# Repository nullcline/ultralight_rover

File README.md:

# ultralight_rover
[design team] CAD files, a PCB, and firmware for an autonomous, and ultra light weight rover

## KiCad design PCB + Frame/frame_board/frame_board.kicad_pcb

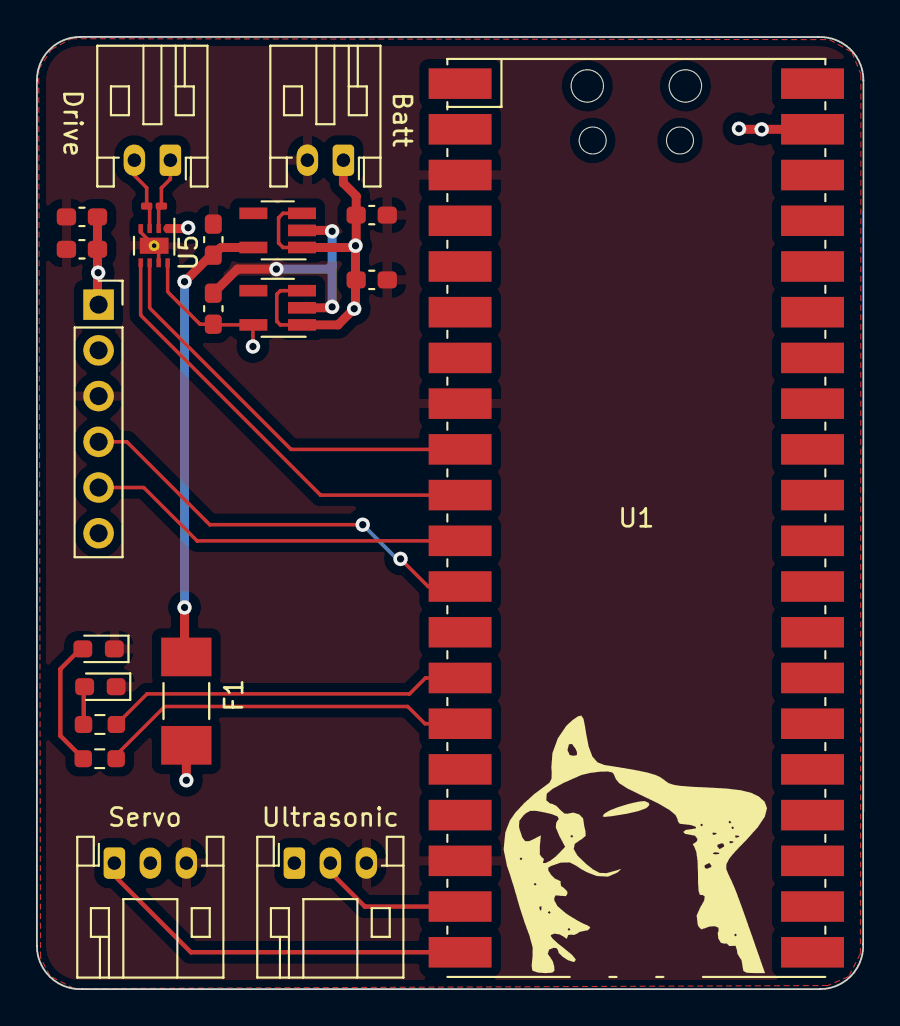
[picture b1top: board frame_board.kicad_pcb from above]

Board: 2 copper layers, 45.9 x 52.9 mm, 21 parts (0 on the bottom side), 17 nets.

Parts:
C1, C2, C21, C22: 10uF; C_0603_1608Metric_Pad1.08x0.95mm_HandSolder
C20: 100nF; C_0603_1608Metric_Pad1.08x0.95mm_HandSolder
C_Bulk1: 1uF; C_0603_1608Metric_Pad1.08x0.95mm_HandSolder
D1, D2: LED; D_0603_1608Metric_Pad1.05x0.95mm_HandSolder
F1: Fuse; FUSC6125X279N
J0: Battery Input; JST_PH_S2B-PH-K_1x02_P2.00mm_Horizontal
J3: BNO055 Breakout; PinSocket_1x06_P2.54mm_Vertical
M2: Drive Motor; JST_PH_S2B-PH-K_1x02_P2.00mm_Horizontal
MotorCap1: 100nF; C_0201_0603Metric_Pad0.64x0.40mm_HandSolder
RLED1, RLED2: 100; R_0603_1608Metric_Pad0.98x0.95mm_HandSolder
Servo: Steering Servo; JST_PH_S3B-PH-K_1x03_P2.00mm_Horizontal
U1: Pico; RPi_Pico_SMD_TH
U2: NCP1117-3.3_SOT223; SOT-23-5_HandSoldering
U3: NCP1117-5.0_SOT223; SOT-23-5_HandSoldering
U5: DRV8212; WSON-8-1EP_2x2mm_P0.5mm_EP0.9x1.6mm_ThermalVias
Ultrasonic: LV-MaxSonar; JST_PH_S3B-PH-K_1x03_P2.00mm_Horizontal

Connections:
+3V3: C2.2, U1.39 (VSYS), U2.2 (VO), U5.8 (VCC), Ultrasonic.1
+5V: C20.2, C_Bulk1.2, F1.2, J3.1, Servo.2 (+), U5.1 (VM)
+BATT: C1.2, C21.2, J0.1, U2.3 (VI), U3.3 (VI)
/GPIO6: U1.9 (GPIO6), U5.6 (IN1)
/GPIO7: U1.10 (GPIO7), U5.5 (IN2)
/GPIO8: J3.5, U1.11 (GPIO8)
/GPIO9: J3.4, U1.12 (GPIO9)
/GPIO10: RLED1.2, U1.14 (GPIO10)
/GPIO11: RLED2.2, U1.15 (GPIO11)
/GPIO14: U1.19 (GPIO14), Ultrasonic.2
/Servo_PWM: Servo.1 (PWM), U1.20 (GPIO15)
GND: C1.1, C2.1, C20.1, C21.1, C22.1, C_Bulk1.1, D1.1 (K), D2.1 (K), J0.2, J3.3, Servo.3 (-), U1.3 (GND), U1.8 (GND), U1.18 (GND), U2.1 (GND), U3.1 (GND), U5.4 (GND), U5.7 (MODE), U5.9 (HeatSink), Ultrasonic.3
unnamed: C22.2, F1.1, U3.2 (VO)
unnamed: M2.1 (+), MotorCap1.2, U5.2 (OUT1)
unnamed: M2.2 (-), MotorCap1.1, U5.3 (OUT2)
unnamed: D1.2 (A), RLED1.1
unnamed: D2.2 (A), RLED2.1

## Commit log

2023-06-26 initial commit of old design
